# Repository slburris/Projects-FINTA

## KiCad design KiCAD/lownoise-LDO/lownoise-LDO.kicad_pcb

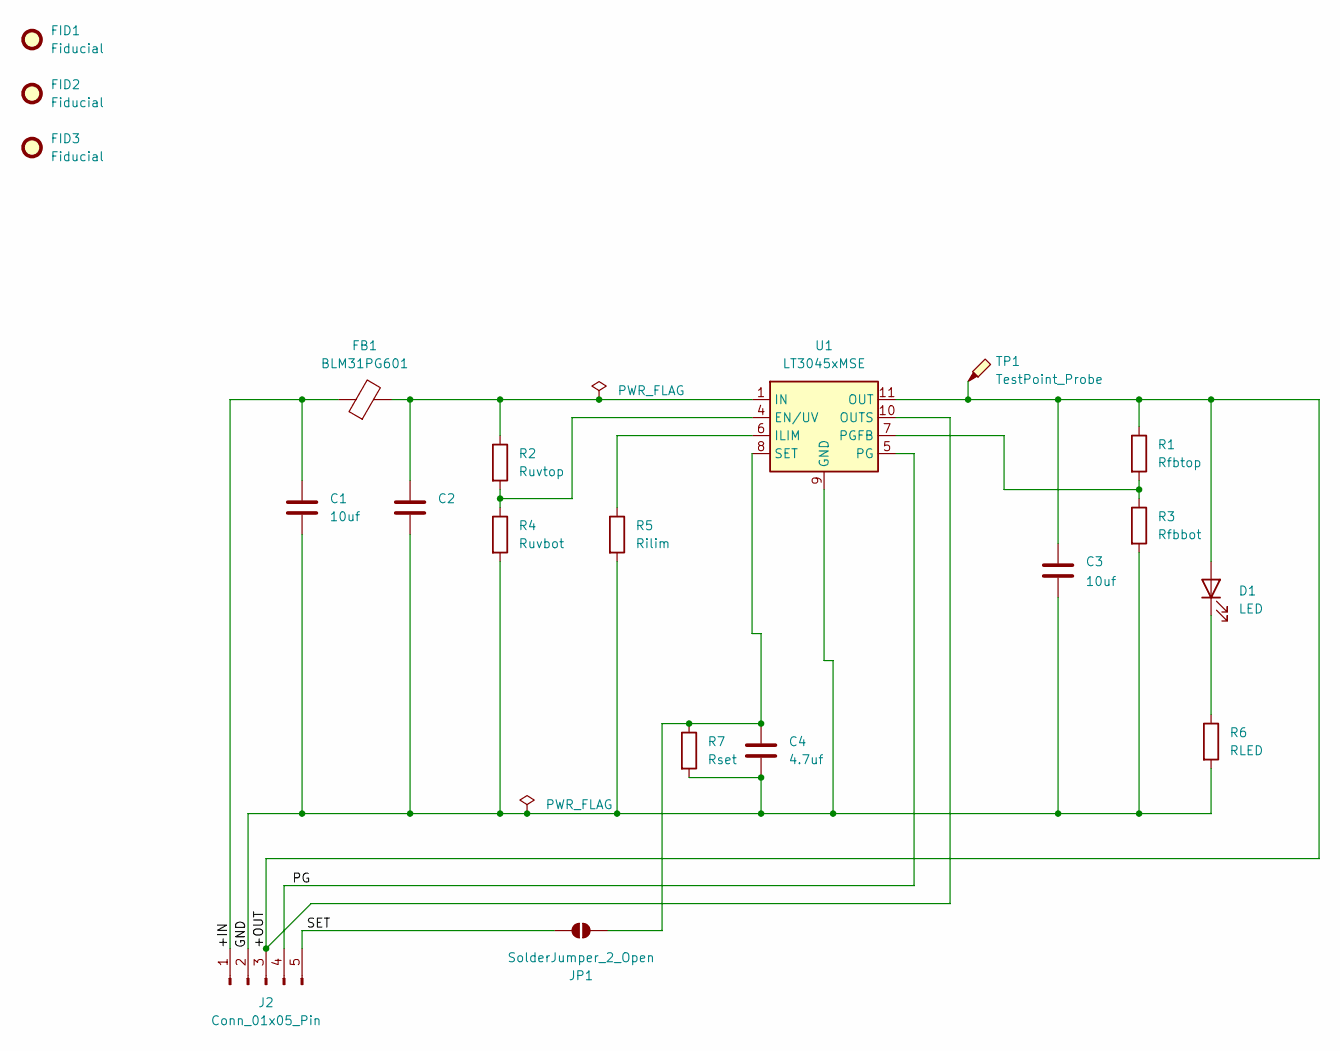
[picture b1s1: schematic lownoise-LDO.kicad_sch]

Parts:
C1, C2, C3: 10uf; C_0603_1608Metric_Pad1.08x0.95mm_HandSolder
C4: 4.7uf; C_0603_1608Metric_Pad1.08x0.95mm_HandSolder
D1: LED; LED_D3.0mm_Horizontal_O1.27mm_Z2.0mm
FB1: BLM31PG601; L_1206_3216Metric_Pad1.22x1.90mm_HandSolder
FID1, FID2, FID3: Fiducial; Fiducial_1mm_Mask2mm
J2: Conn_01x05_Pin; PinHeader_1x05_P2.00mm_Horizontal
JP1: SolderJumper_2_Open; SolderJumper-2_P1.3mm_Open_TrianglePad1.0x1.5mm
R1: Rfbtop; R_0603_1608Metric_Pad0.98x0.95mm_HandSolder
R2: Ruvtop; R_0603_1608Metric_Pad0.98x0.95mm_HandSolder
R3: Rfbbot; R_0603_1608Metric_Pad0.98x0.95mm_HandSolder
R4: Ruvbot; R_0603_1608Metric_Pad0.98x0.95mm_HandSolder
R5: Rilim; R_0603_1608Metric_Pad0.98x0.95mm_HandSolder
R6: RLED; R_0603_1608Metric_Pad0.98x0.95mm_HandSolder
R7: Rset; R_0603_1608Metric_Pad0.98x0.95mm_HandSolder
TP1: TestPoint_Probe; TestPoint_Pad_2.0x2.0mm
U1: LT3045xMSE; MSOP-12-1EP_3x4.039mm_P0.65mm_EP1.651x2.845mm

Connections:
/+IN: C1.1, FB1.1, J2.1
/+OUT: C3.1, D1.2 (A), J2.3, R1.1, TP1.1, U1.10 (OUTS), U1.11 (OUT), U1.12 (OUT)
/GND: C1.2, C2.2, C3.2, C4.2, J2.2, R3.2, R4.2, R5.2, R6.2, R7.2, U1.9 (GND), U1.13 (GND)
/PG: J2.4, U1.5 (PG)
/SET: J2.5, JP1.1 (A)
unnamed: C2.1, FB1.2, R2.1, U1.1 (IN), U1.2 (IN), U1.3 (IN)
unnamed: D1.1 (K), R6.1
unnamed: C4.1, JP1.2 (B), R7.1, U1.8 (SET)
unnamed: R2.2, R4.1, U1.4 (EN/UV)
unnamed: R5.1, U1.6 (ILIM)
unnamed: R1.2, R3.1, U1.7 (PGFB)

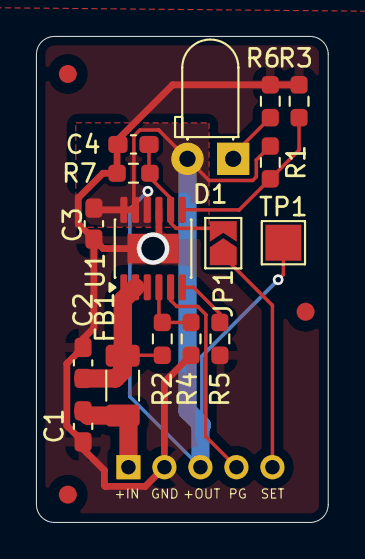
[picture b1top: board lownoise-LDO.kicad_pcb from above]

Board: 2 copper layers, 16.2 x 27.0 mm, 20 parts (1 on the bottom side), 11 nets.

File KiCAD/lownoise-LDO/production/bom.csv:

Designator,Footprint,Quantity,Value,LCSC Part #
"C1, C2, C3",0603,3,10uf,
C4,0603,1,4.7uf,
D1,LED_D3.0mm_Horizontal_O1.27mm_Z2.0mm,1,LED,
FB1,1206,1,BLM31PG601,
J2,PinHeader_1x05_P2.00mm_Horizontal,1,Conn_01x05_Pin,
R1,0603,1,Rfbtop,
R2,0603,1,Ruvtop,
R3,0603,1,Rfbbot,
R4,0603,1,Ruvbot,
R5,0603,1,Rilim,
R6,0603,1,RLED,
R7,0603,1,Rset,
TP1,TestPoint_Pad_2.0x2.0mm,1,TestPoint_Probe,
U1,MSOP-12-1EP_3x4.039mm_P0.65mm_EP1.651x2.845mm,1,LT3045xMSE,

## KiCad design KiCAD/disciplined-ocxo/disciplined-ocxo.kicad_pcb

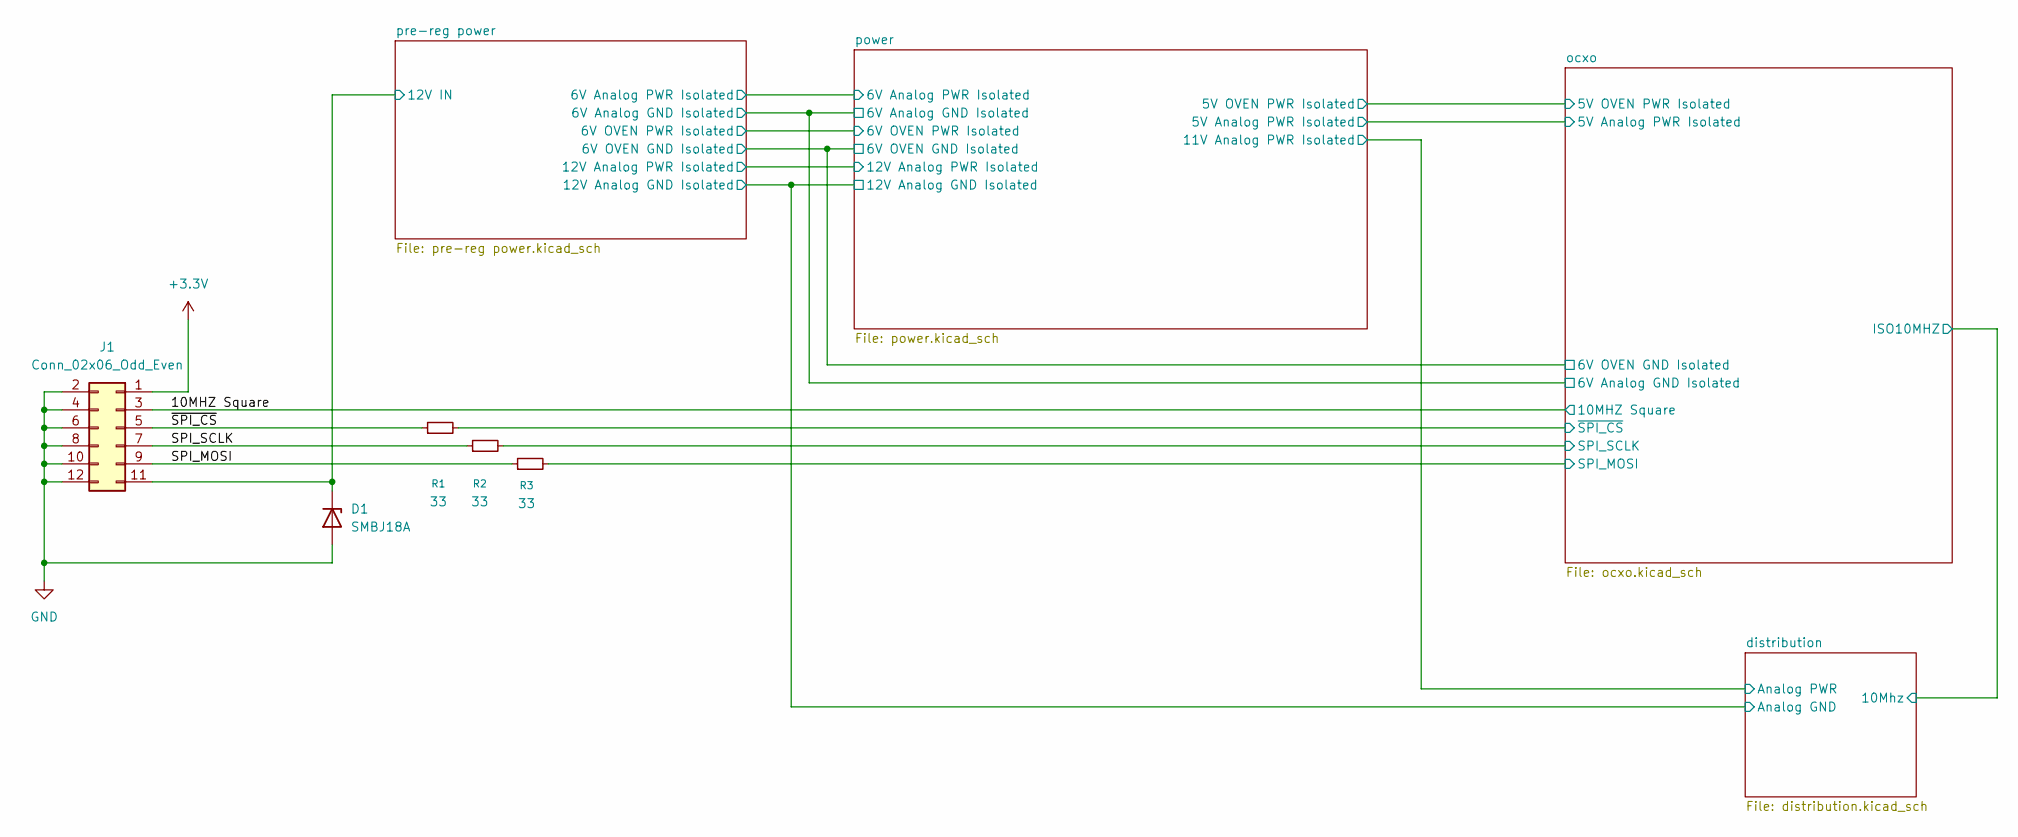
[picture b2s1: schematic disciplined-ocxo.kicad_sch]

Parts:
D1: SMBJ18A; D_SMB_Handsoldering
J1: Conn_02x06_Odd_Even; PinHeader_2x06_P2.54mm_Horizontal
R1, R2, R3: 33; R_1206_3216Metric_Pad1.30x1.75mm_HandSolder

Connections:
+3.3V: J1.1; also elsewhere on the board
/10MHZ Square: J1.3; also elsewhere on the board
/SPI_MOSI: J1.9, R3.1
/SPI_SCLK: J1.7, R2.1
/ocxo/SPI_MOSI: R3.2; also elsewhere on the board
/ocxo/SPI_SCLK: R2.2; also elsewhere on the board
/ocxo/~SPI_CS: R1.2; also elsewhere on the board
/pre-reg power/12V IN: D1.1 (K), J1.11; also elsewhere on the board
/~SPI_CS: J1.5, R1.1
GND: D1.2 (A), J1.2, J1.4, J1.6, J1.8, J1.10, J1.12; also elsewhere on the board

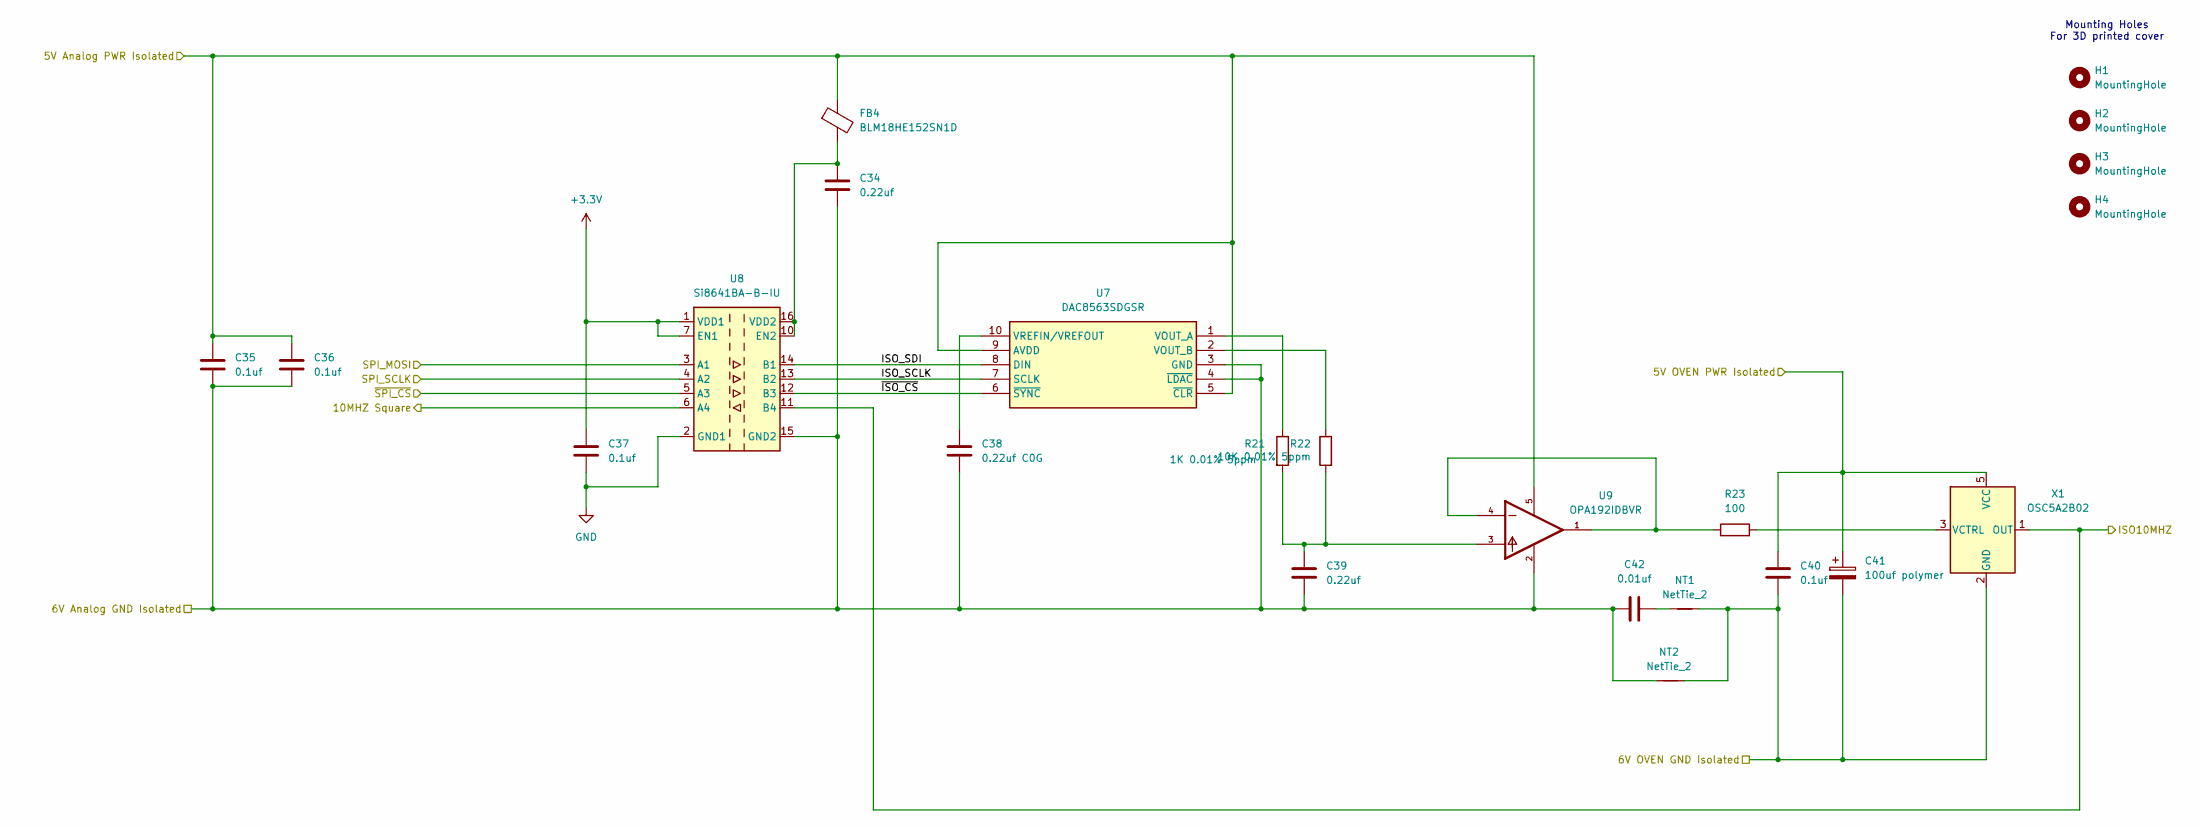
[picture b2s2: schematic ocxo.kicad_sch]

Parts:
C34, C39: 0.22uf; C_1206_3216Metric_Pad1.33x1.80mm_HandSolder
C35, C36, C37, C40: 0.1uf; C_0603_1608Metric_Pad1.08x0.95mm_HandSolder
C38: 0.22uf C0G; C_0603_1608Metric_Pad1.08x0.95mm_HandSolder
C41: 100uf polymer; CP_Radial_D5.0mm_P2.00mm
C42: 0.01uf; C_0603_1608Metric_Pad1.08x0.95mm_HandSolder
FB4: BLM18HE152SN1D; L_0603_1608Metric_Pad1.05x0.95mm_HandSolder
H1, H2, H3, H4: MountingHole; MountingHole_3.2mm_M3
NT1, NT2: NetTie_2; NetTie-2_SMD_Pad0.5mm
R21: 1K 0.01% 5ppm; R_0805_2012Metric_Pad1.20x1.40mm_HandSolder
R22: 10K 0.01% 5ppm; R_0805_2012Metric_Pad1.20x1.40mm_HandSolder
R23: 100; R_1206_3216Metric_Pad1.30x1.75mm_HandSolder
U7: DAC8563SDGSR; SOP50P490X110-10N; Manufacturer_Part_Number DAC8563SDGSR; Mouser Part Number 595-DAC8563SDGSR
U8: Si8641BA-B-IU; QSOP-16_3.9x4.9mm_P0.635mm
U9: OPA192IDBVR; SOT95P280X145-5N; PARTREV F
X1: OSC5A2B02; CTI-OSC-25x25

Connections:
+3.3V: C37.2, U8.1 (VDD1), U8.7 (EN1); also elsewhere on the board
/10MHZ Square: U8.6 (A4); also elsewhere on the board
/distribution/10Mhz: U8.11 (B4), X1.1 (OUT); also elsewhere on the board
/ocxo/5V Analog PWR Isolated: C35.1, C36.1, FB4.1, U7.5 (~CLR), U7.9 (AVDD), U9.5; also elsewhere on the board
/ocxo/5V OVEN PWR Isolated: C40.1, C41.1, X1.5 (VCC); also elsewhere on the board
/ocxo/6V Analog GND Isolated: C34.2, C35.2, C36.2, C38.2, C39.2, C42.1, NT2.1, U7.3 (GND), U7.4 (~LDAC), U8.9 (GND2), U8.15 (GND2), U9.2; also elsewhere on the board
/ocxo/6V OVEN GND Isolated: C40.2, C41.2, NT1.2, NT2.2, X1.2 (GND); also elsewhere on the board
/ocxo/ISO_SCLK: U7.7 (SCLK), U8.13 (B2)
/ocxo/ISO_SDI: U7.8 (DIN), U8.14 (B1)
/ocxo/SPI_MOSI: U8.3 (A1); also elsewhere on the board
/ocxo/SPI_SCLK: U8.4 (A2); also elsewhere on the board
/ocxo/~ISO_CS: U7.6 (~SYNC), U8.12 (B3)
/ocxo/~SPI_CS: U8.5 (A3); also elsewhere on the board
GND: C37.1, U8.2 (GND1), U8.8 (GND1); also elsewhere on the board
unnamed: C39.1, R21.2, R22.2, U9.3
unnamed: C42.2, NT1.1
unnamed: R23.1, U9.1, U9.4
unnamed: R21.1, U7.1 (VOUT_A)
unnamed: R22.1, U7.2 (VOUT_B)
unnamed: C38.1, U7.10 (VREFIN/VREFOUT)
unnamed: C34.1, FB4.2, U8.10 (EN2), U8.16 (VDD2)
unnamed: R23.2, X1.3 (VCTRL)

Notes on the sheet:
Mounting Holes For 3D printed cover

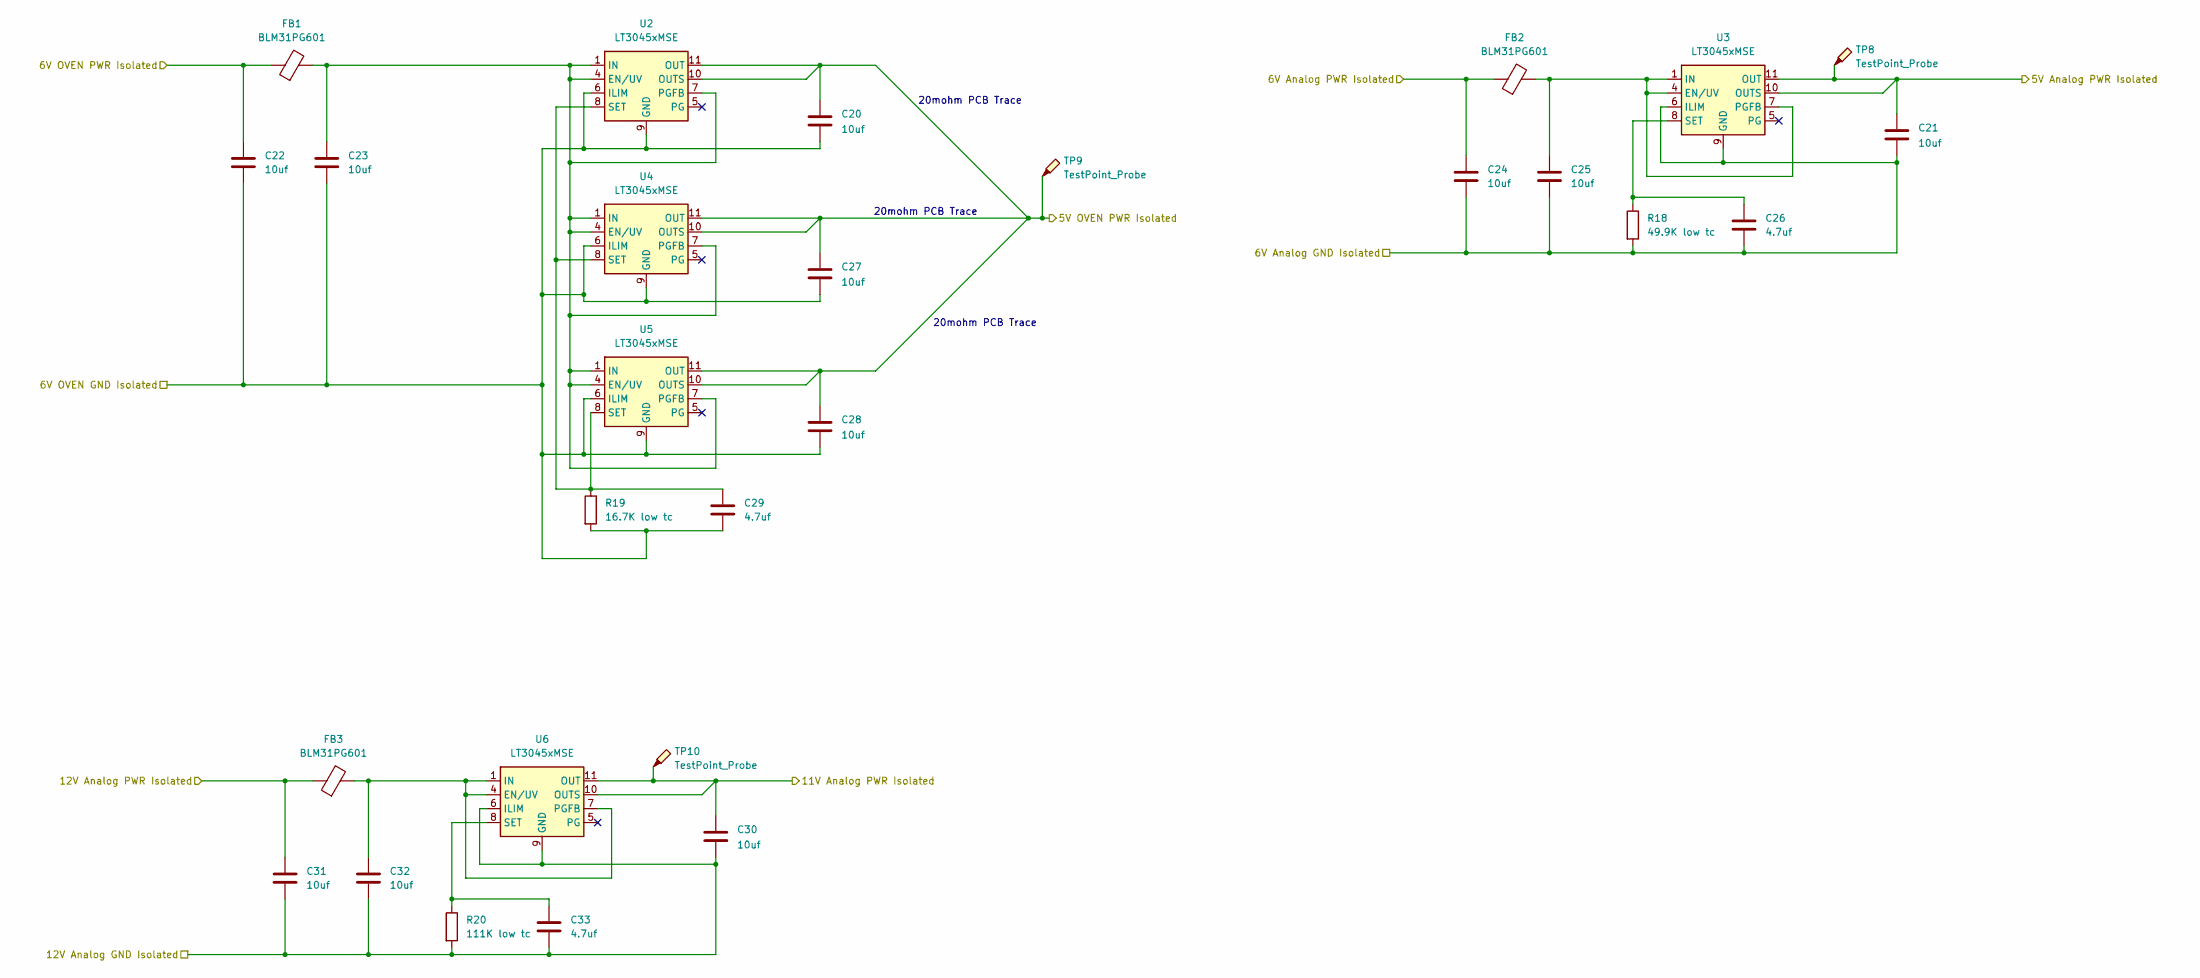
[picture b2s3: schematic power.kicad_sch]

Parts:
C20, C21, C22, C23, C24, C25, C27, C28, C30, C31, C32: 10uf; C_0603_1608Metric_Pad1.08x0.95mm_HandSolder
C26, C29, C33: 4.7uf; C_0603_1608Metric_Pad1.08x0.95mm_HandSolder
FB1, FB2, FB3: BLM31PG601; L_1206_3216Metric_Pad1.22x1.90mm_HandSolder
R18: 49.9K low tc; R_0603_1608Metric_Pad0.98x0.95mm_HandSolder
R19: 16.7K low tc; R_0603_1608Metric_Pad0.98x0.95mm_HandSolder
R20: 111K low tc; R_0603_1608Metric_Pad0.98x0.95mm_HandSolder
TP8, TP9, TP10: TestPoint_Probe; TestPoint_Pad_2.0x2.0mm
U2, U3, U4, U5, U6: LT3045xMSE; MSOP-12-1EP_3x4.039mm_P0.65mm_EP1.651x2.845mm

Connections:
/distribution/Analog GND: C30.2, C31.2, C32.2, C33.2, R20.2, U6.6 (ILIM), U6.9 (GND), U6.13 (GND); also elsewhere on the board
/distribution/Analog PWR: C30.1, TP10.1, U6.10 (OUTS), U6.11 (OUT), U6.12 (OUT); also elsewhere on the board
/ocxo/5V Analog PWR Isolated: C21.1, TP8.1, U3.10 (OUTS), U3.11 (OUT), U3.12 (OUT); also elsewhere on the board
/ocxo/5V OVEN PWR Isolated: C20.1, C27.1, C28.1, TP9.1, U2.10 (OUTS), U2.11 (OUT), U2.12 (OUT), U4.10 (OUTS), U4.11 (OUT), U4.12 (OUT), U5.10 (OUTS), U5.11 (OUT), U5.12 (OUT); also elsewhere on the board
/ocxo/6V Analog GND Isolated: C21.2, C24.2, C25.2, C26.2, R18.2, U3.6 (ILIM), U3.9 (GND), U3.13 (GND); also elsewhere on the board
/ocxo/6V OVEN GND Isolated: C20.2, C22.2, C23.2, C27.2, C28.2, C29.2, R19.2, U2.6 (ILIM), U2.9 (GND), U2.13 (GND), U4.6 (ILIM), U4.9 (GND), U4.13 (GND), U5.6 (ILIM), U5.9 (GND), U5.13 (GND); also elsewhere on the board
/power/6V Analog PWR Isolated: C24.1, FB2.1; also elsewhere on the board
/power/6V OVEN PWR Isolated: C22.1, FB1.1; also elsewhere on the board
/power/12V Analog PWR Isolated: C31.1, FB3.1; also elsewhere on the board
unnamed: C23.1, FB1.2, U2.1 (IN), U2.2 (IN), U2.3 (IN), U2.4 (EN/UV), U2.7 (PGFB), U4.1 (IN), U4.2 (IN), U4.3 (IN), U4.4 (EN/UV), U4.7 (PGFB), U5.1 (IN), U5.2 (IN), U5.3 (IN), U5.4 (EN/UV), U5.7 (PGFB)
unnamed: C29.1, R19.1, U2.8 (SET), U4.8 (SET), U5.8 (SET)
unnamed: C25.1, FB2.2, U3.1 (IN), U3.2 (IN), U3.3 (IN), U3.4 (EN/UV), U3.7 (PGFB)
unnamed: C26.1, R18.1, U3.8 (SET)
unnamed: C32.1, FB3.2, U6.1 (IN), U6.2 (IN), U6.3 (IN), U6.4 (EN/UV), U6.7 (PGFB)
unnamed: C33.1, R20.1, U6.8 (SET)

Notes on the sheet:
20mohm PCB Trace

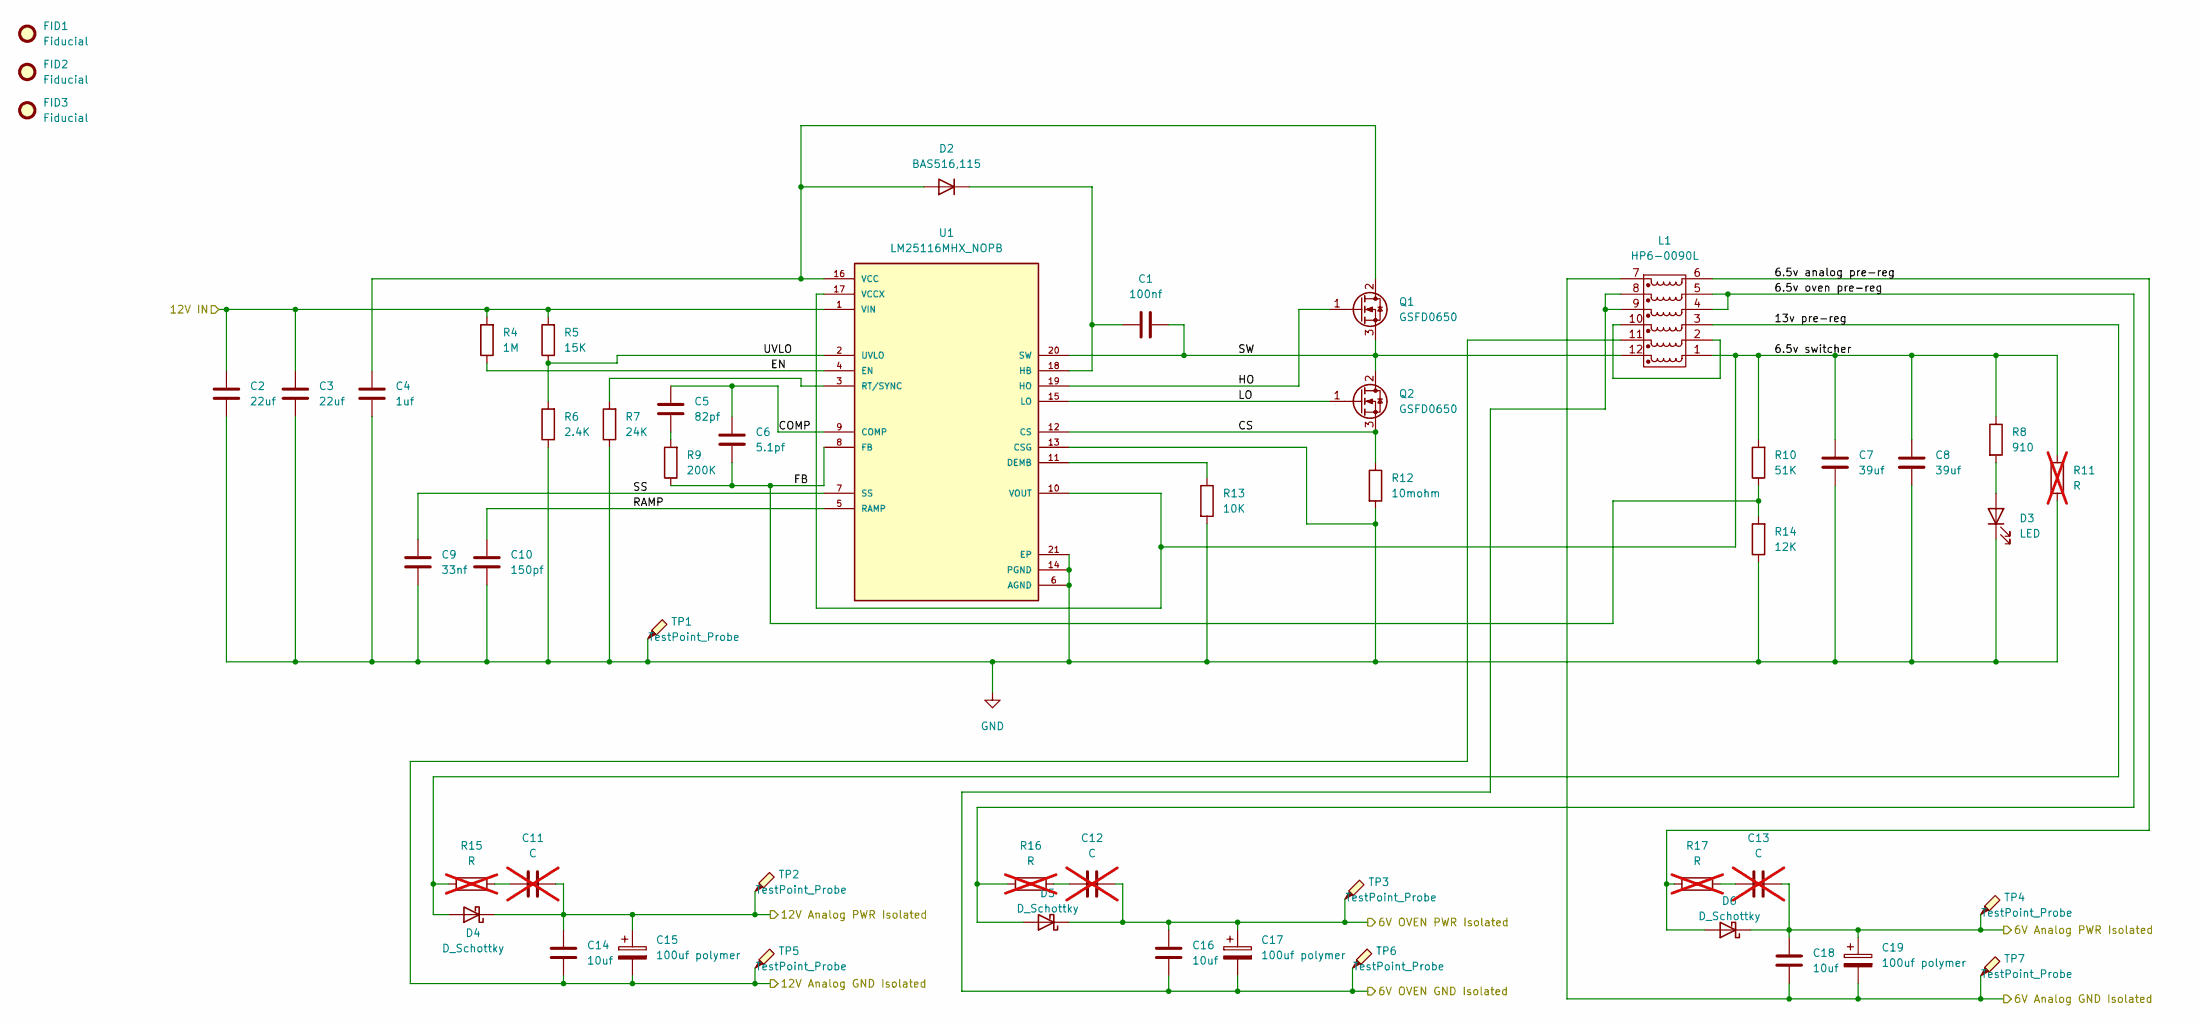
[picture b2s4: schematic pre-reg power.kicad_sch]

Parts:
C1: 100nf; C_0603_1608Metric_Pad1.08x0.95mm_HandSolder
C2, C3: 22uf; C_1206_3216Metric_Pad1.33x1.80mm_HandSolder
C4: 1uf; C_0603_1608Metric_Pad1.08x0.95mm_HandSolder
C5: 82pf; C_0603_1608Metric_Pad1.08x0.95mm_HandSolder
C6: 5.1pf; C_0603_1608Metric_Pad1.08x0.95mm_HandSolder
C7, C8: 39uf; C_1206_3216Metric_Pad1.33x1.80mm_HandSolder
C9: 33nf; C_0603_1608Metric_Pad1.08x0.95mm_HandSolder
C10: 150pf; C_0603_1608Metric_Pad1.08x0.95mm_HandSolder
C11, C12, C13: C; C_1206_3216Metric_Pad1.33x1.80mm_HandSolder; not fitted
C14, C16, C18: 10uf; C_1206_3216Metric_Pad1.33x1.80mm_HandSolder
C15, C17, C19: 100uf polymer; CP_Radial_D5.0mm_P2.00mm
D2: BAS516,115; D_SOD-523
D3: LED; LED_0805_2012Metric_Pad1.15x1.40mm_HandSolder
D4, D5, D6: D_Schottky; D_SMB_Handsoldering
FID1, FID2, FID3: Fiducial; Fiducial_1mm_Mask3mm
L1: HP6-0090L
Q1, Q2: GSFD0650; TO-252-2
R4: 1M; R_0603_1608Metric_Pad0.98x0.95mm_HandSolder
R5: 15K; R_0603_1608Metric_Pad0.98x0.95mm_HandSolder
R6: 2.4K; R_0603_1608Metric_Pad0.98x0.95mm_HandSolder
R7: 24K; R_0603_1608Metric_Pad0.98x0.95mm_HandSolder
R8: 910; R_1206_3216Metric_Pad1.30x1.75mm_HandSolder
R9: 200K; R_0603_1608Metric_Pad0.98x0.95mm_HandSolder
R10: 51K; R_0603_1608Metric_Pad0.98x0.95mm_HandSolder
R11, R15, R16, R17: R; R_1206_3216Metric_Pad1.30x1.75mm_HandSolder; not fitted
R12: 10mohm; R_1206_3216Metric_Pad1.30x1.75mm_HandSolder
R13: 10K; R_1206_3216Metric_Pad1.30x1.75mm_HandSolder
R14: 12K; R_0603_1608Metric_Pad0.98x0.95mm_HandSolder
TP1, TP2, TP3, TP4, TP5, TP6, TP7: TestPoint_Probe; TestPoint_Pad_2.0x2.0mm
U1: LM25116MHX_NOPB; SOP65P640X110-21N; PARTREV E

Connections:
/distribution/Analog GND: C14.2, C15.2, L1.11, TP5.1; also elsewhere on the board
/ocxo/6V Analog GND Isolated: C18.2, C19.2, L1.7, TP7.1; also elsewhere on the board
/ocxo/6V OVEN GND Isolated: C16.2, C17.2, L1.8, L1.9, TP6.1; also elsewhere on the board
/power/6V Analog PWR Isolated: C13.2, C18.1, C19.1, D6.1 (K), TP4.1; also elsewhere on the board
/power/6V OVEN PWR Isolated: C12.2, C16.1, C17.1, D5.1 (K), TP3.1; also elsewhere on the board
/power/12V Analog PWR Isolated: C11.2, C14.1, C15.1, D4.1 (K), TP2.1; also elsewhere on the board
/pre-reg power/6.5v analog pre-reg: D6.2 (A), L1.6, R17.1
/pre-reg power/6.5v oven pre-reg: D5.2 (A), L1.4, L1.5, R16.1
/pre-reg power/6.5v switcher: C7.1, C8.1, L1.1, R8.1, R10.2, R11.1, U1.10 (VOUT), U1.17 (VCCX)
/pre-reg power/12V IN: C2.1, C3.1, R4.2, R5.2, U1.1 (VIN); also elsewhere on the board
/pre-reg power/13v pre-reg: D4.2 (A), L1.3, R15.1
/pre-reg power/COMP: C5.1, C6.1, U1.9 (COMP)
/pre-reg power/CS: Q2.3 (S), R12.1, U1.12 (CS)
/pre-reg power/EN: R4.1, U1.4 (EN)
/pre-reg power/FB: C6.2, R9.1, R10.1, R14.2, U1.8 (FB)
/pre-reg power/HO: Q1.1 (G), U1.19 (HO)
/pre-reg power/LO: Q2.1 (G), U1.15 (LO)
/pre-reg power/RAMP: C10.1, U1.5 (RAMP)
/pre-reg power/SS: C9.1, U1.7 (SS)
/pre-reg power/SW: C1.2, L1.12, Q1.3 (S), Q2.2 (D), U1.20 (SW)
/pre-reg power/UVLO: R5.1, R6.2, U1.2 (UVLO)
GND: C2.2, C3.2, C4.2, C7.2, C8.2, C9.2, C10.2, D3.1 (K), R6.1, R7.1, R11.2, R12.2, R13.2, R14.1, TP1.1, U1.6 (AGND), U1.13 (CSG), U1.14 (PGND), U1.21 (EP); also elsewhere on the board
unnamed: C5.2, R9.2
unnamed: C11.1, R15.2
unnamed: C12.1, R16.2
unnamed: C13.1, R17.2
unnamed: C4.1, D2.2 (A), Q1.2 (D), U1.16 (VCC)
unnamed: C1.1, D2.1 (K), U1.18 (HB)
unnamed: D3.2 (A), R8.2
unnamed: L1.2, L1.10
unnamed: R13.1, U1.11 (DEMB)
unnamed: R7.2, U1.3 (RT/SYNC)

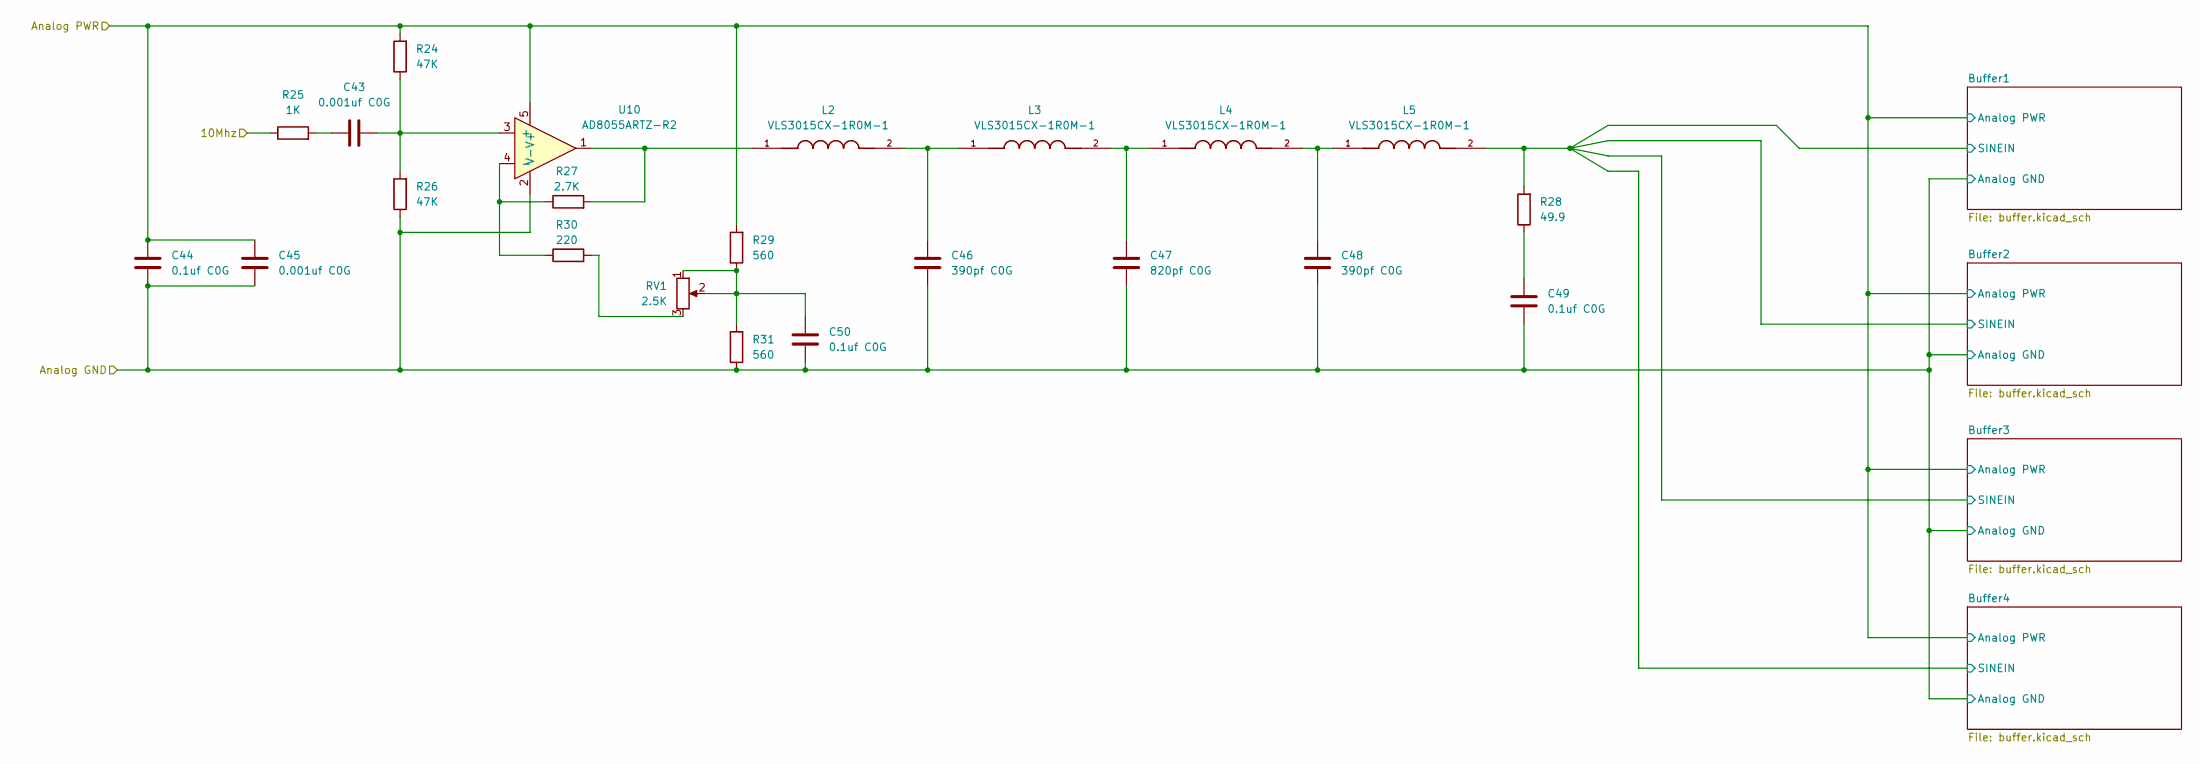
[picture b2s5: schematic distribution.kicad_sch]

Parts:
C43, C45: 0.001uf C0G; C_1206_3216Metric_Pad1.33x1.80mm_HandSolder
C44, C49, C50: 0.1uf C0G; C_1206_3216Metric_Pad1.33x1.80mm_HandSolder
C46, C48: 390pf C0G; C_1206_3216Metric_Pad1.33x1.80mm_HandSolder
C47: 820pf C0G; C_1206_3216Metric_Pad1.33x1.80mm_HandSolder
L2, L3, L4, L5: VLS3015CX-1R0M-1; IND_VLS3015CX-1R0M-1; PARTREV N/A
R24, R26: 47K; R_1206_3216Metric_Pad1.30x1.75mm_HandSolder
R25: 1K; R_1206_3216Metric_Pad1.30x1.75mm_HandSolder
R27: 2.7K; R_1206_3216Metric_Pad1.30x1.75mm_HandSolder
R28: 49.9; R_1206_3216Metric_Pad1.30x1.75mm_HandSolder
R29, R31: 560; R_1206_3216Metric_Pad1.30x1.75mm_HandSolder
R30: 220; R_1206_3216Metric_Pad1.30x1.75mm_HandSolder
RV1: 2.5K; Potentiometer_Bourns_3296W_Vertical
U10: AD8055ARTZ-R2; SOT95P290X145-5N; MPN AD8055ARTZ-R2

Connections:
/distribution/10Mhz: R25.1; also elsewhere on the board
/distribution/Analog GND: C44.2, C45.2, C46.2, C47.2, C48.2, C49.2, C50.2, R26.1, R31.1, U10.2 (V-); also elsewhere on the board
/distribution/Analog PWR: C44.1, C45.1, R24.2, R29.2, U10.5 (V+); also elsewhere on the board
/distribution/Buffer1/SINEIN: L5.2, R28.2; also elsewhere on the board
unnamed: C43.1, R25.2
unnamed: C46.1, L2.2, L3.1
unnamed: C47.1, L3.2, L4.1
unnamed: C48.1, L4.2, L5.1
unnamed: C49.1, R28.1
unnamed: C50.1, R29.1, R31.2, RV1.1, RV1.2
unnamed: L2.1, R27.2, U10.1
unnamed: R30.2, RV1.3
unnamed: C43.2, R24.1, R26.2, U10.3 (+)
unnamed: R27.1, R30.1, U10.4 (-)

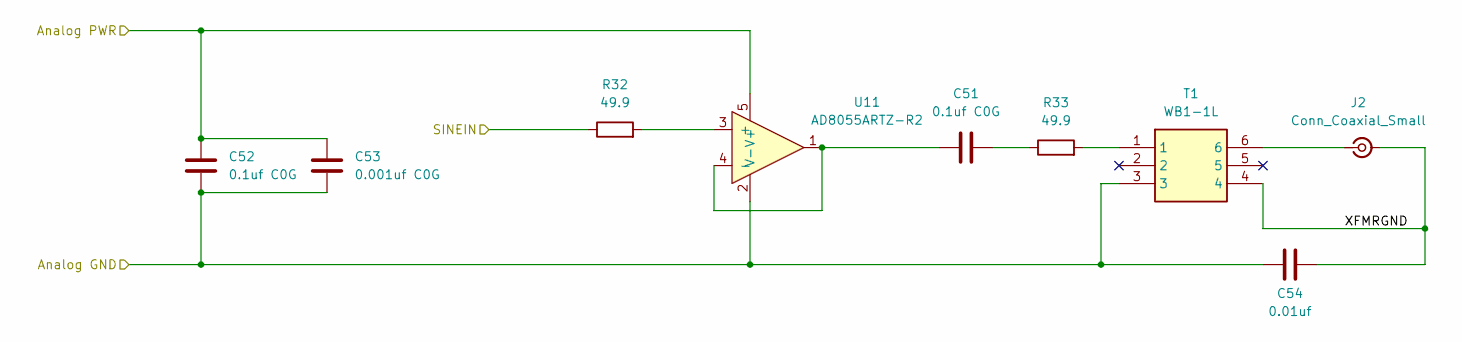
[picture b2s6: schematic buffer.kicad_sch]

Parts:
C51, C52: 0.1uf C0G; C_1206_3216Metric_Pad1.33x1.80mm_HandSolder
C53: 0.001uf C0G; C_1206_3216Metric_Pad1.33x1.80mm_HandSolder
C54: 0.01uf; C_1206_3216Metric_Pad1.33x1.80mm_HandSolder
J2: Conn_Coaxial_Small; SMA_Amphenol_132291-12_Vertical
R32, R33: 49.9; R_1206_3216Metric_Pad1.30x1.75mm_HandSolder
T1: WB1-1L; DIP762W64P254L826H572Q6N; Manufacturer_Part_Number WB1-1L; Mouser Part Number 994-WB1-1L
U11: AD8055ARTZ-R2; SOT95P290X145-5N; MPN AD8055ARTZ-R2

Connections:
/distribution/Analog GND: C52.2, C53.2, C54.1, T1.3, U11.2 (V-); also elsewhere on the board
/distribution/Analog PWR: C52.1, C53.1, U11.5 (V+); also elsewhere on the board
/distribution/Buffer1/SINEIN: R32.1; also elsewhere on the board
/distribution/Buffer1/XFMRGND: C54.2, J2.2 (Ext), T1.4
unnamed: C51.2, R33.1
unnamed: J2.1 (In), T1.6
unnamed: R33.2, T1.1
unnamed: R32.2, U11.3 (+)
unnamed: C51.1, U11.1, U11.4 (-)

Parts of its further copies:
C55, C56, C59, C60, C63, C64: 0.1uf C0G; C_1206_3216Metric_Pad1.33x1.80mm_HandSolder
C57, C61, C65: 0.001uf C0G; C_1206_3216Metric_Pad1.33x1.80mm_HandSolder
C58, C62, C66: 0.01uf; C_1206_3216Metric_Pad1.33x1.80mm_HandSolder
J3, J4, J5: Conn_Coaxial_Small; SMA_Amphenol_132291-12_Vertical
R34, R35, R36, R37, R38, R39: 49.9; R_1206_3216Metric_Pad1.30x1.75mm_HandSolder
T2, T3, T4: WB1-1L; DIP762W64P254L826H572Q6N; Manufacturer_Part_Number WB1-1L; Mouser Part Number 994-WB1-1L
U12, U13, U14: AD8055ARTZ-R2; SOT95P290X145-5N; MPN AD8055ARTZ-R2

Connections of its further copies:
/distribution/Analog GND: C56.2, C57.2, C58.1, C60.2, C61.2, C62.1, C64.2, C65.2, C66.1, T2.3, T3.3, T4.3, U12.2 (V-), U13.2 (V-), U14.2 (V-); also elsewhere on the board
/distribution/Analog PWR: C56.1, C57.1, C60.1, C61.1, C64.1, C65.1, U12.5 (V+), U13.5 (V+), U14.5 (V+); also elsewhere on the board
/distribution/Buffer1/SINEIN: R34.1, R36.1, R38.1; also elsewhere on the board
/distribution/Buffer2/XFMRGND: C58.2, J3.2 (Ext), T2.4
/distribution/Buffer3/XFMRGND: C62.2, J4.2 (Ext), T3.4
/distribution/Buffer4/XFMRGND: C66.2, J5.2 (Ext), T4.4
unnamed: C55.2, R35.1
unnamed: C59.2, R37.1
unnamed: C63.2, R39.1
unnamed: J3.1 (In), T2.6
unnamed: J4.1 (In), T3.6
unnamed: J5.1 (In), T4.6
unnamed: R35.2, T2.1
unnamed: R37.2, T3.1
unnamed: R39.2, T4.1
unnamed: R34.2, U12.3 (+)
unnamed: C55.1, U12.1, U12.4 (-)
unnamed: R36.2, U13.3 (+)
unnamed: C59.1, U13.1, U13.4 (-)
unnamed: R38.2, U14.3 (+)
unnamed: C63.1, U14.1, U14.4 (-)

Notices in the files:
KiCAD/IRIG/IRIG.kicad_pcb:
CERN-OHL-S v2
parts and their libraries:
COPYRIGHT: Copyright C 2016 Accelerated Designs. All rights reserved
